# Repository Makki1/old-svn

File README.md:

# old-svn
# mainly old stuff but maybe interesting, owslave parasitic, Gira-RM 1w Interface, 1w DS2423 with attiny84..

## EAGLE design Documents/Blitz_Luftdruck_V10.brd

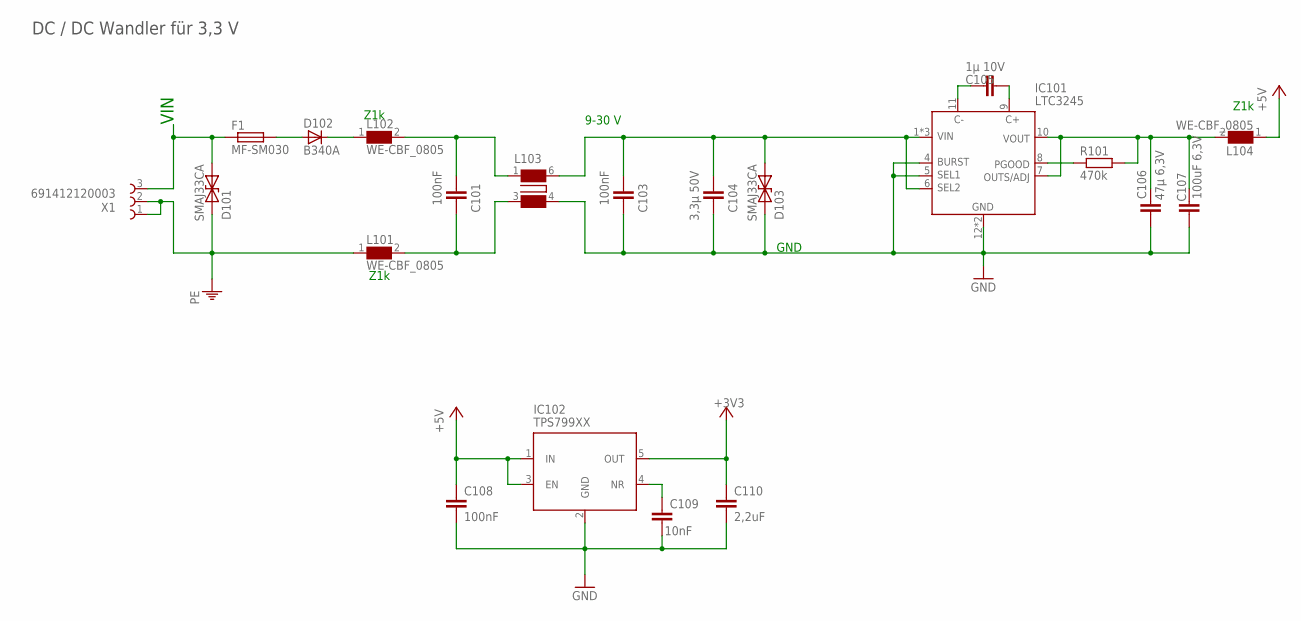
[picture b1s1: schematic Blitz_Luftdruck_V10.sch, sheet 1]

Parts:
C101, C103, C108: 100nF; C0603
C104: 3,3µ 50V; C1210TDK280
C105: 1µ 10V; C0402MUR55
C106: 47µ 6,3V; C0805TDK100
C107: 100uF 6,3V; C1206TDK180
C109: 10nF; C0402MUR55
C110: 2,2uF; C0603
D101, D103: SMAJ33CA; DIOMNP4326X262N
D102: B340A; DIOM5226X230N
F1: MF-SM030; MF-SMX
IC101: LTC3245; PSON50P400X300X80-13N
IC102: TPS799XX; SOT95P280X110-5N
L101, L102, L104: WE-CBF_0805; INDC2012X110N
L103: WE-SL3_744252...
R101: 470k; R0402
X1: 691412120003

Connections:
+3V3: C110.1, IC102.5 (OUT); also elsewhere on the board
+5V: C108.1, IC102.1 (IN), IC102.3 (EN), L104.1; also elsewhere on the board
GND: C103.1, C104.1, C106.2, C107.2, C108.2, C109.2, C110.2, D103.1 (A), IC101.4 (BURST), IC101.5 (SEL1), IC101.12 (GND), IC101.13 (GND), IC102.2 (GND), L103.4 (2); also elsewhere on the board
LTC3245C+: C105.2, IC101.9 (C+)
LTC3245C-: C105.1, IC101.11 (C-)
LTC3245VIN: C103.2, C104.2, D103.2 (C), IC101.1 (VIN), IC101.2 (VIN), IC101.3 (VIN), IC101.6 (SEL2), L103.6 (4)
LTC3245_VOUT: C106.1, C107.1, IC101.7 (ADJ), IC101.10 (VOUT), L104.2, R101.2
unnamed: D102.A, F1.2
unnamed: C101.1, L101.2, L103.3 (1)
unnamed: C101.2, L102.2, L103.1 (3)
unnamed: D102.C, L102.1
unnamed: IC101.8 (PGOOD), R101.1
unnamed: C109.1, IC102.4 (NR)
PE: D101.1 (A), L101.1, X1.1, X1.2; also elsewhere on the board
VIN: D101.2 (C), F1.1, X1.3; also elsewhere on the board

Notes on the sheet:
GND
9-30 V
Z1k
DC / DC Wandler für 3,3 V
VIN

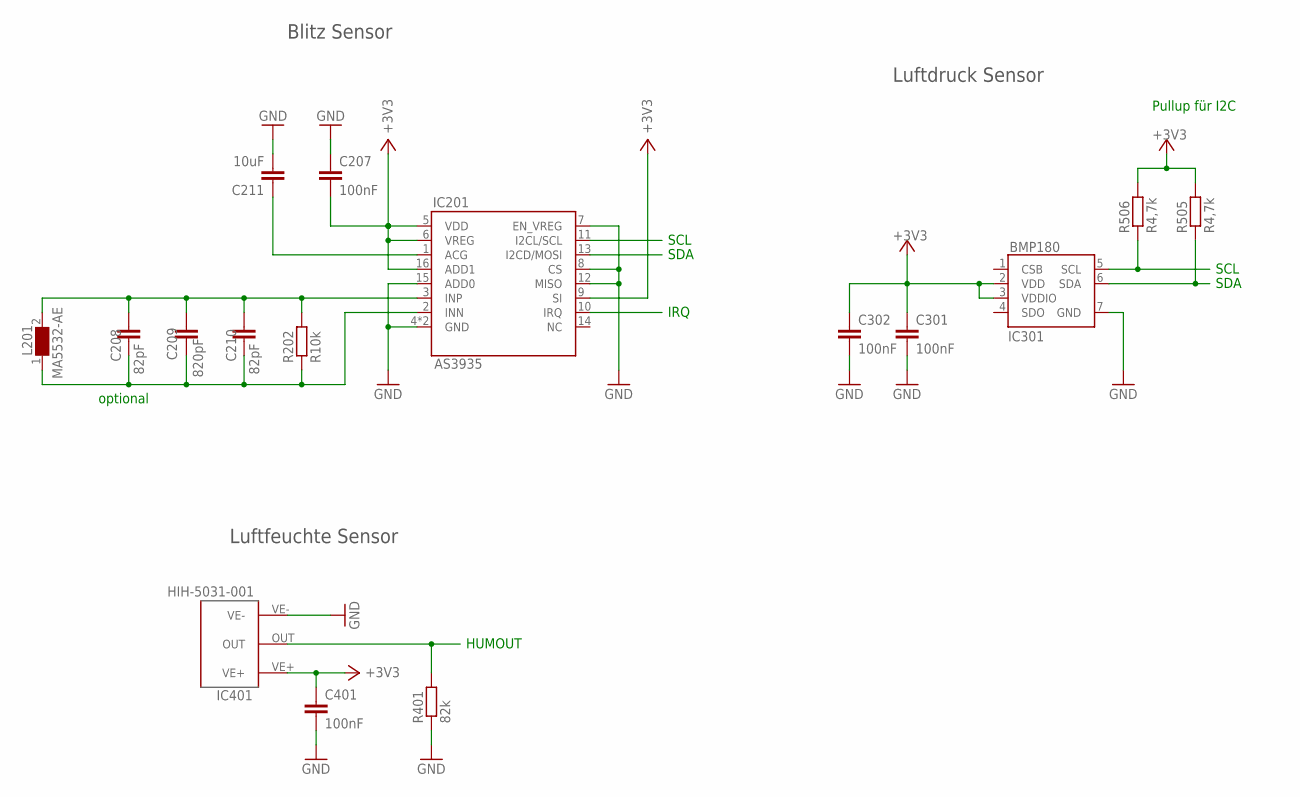
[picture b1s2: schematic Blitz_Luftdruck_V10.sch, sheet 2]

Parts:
C207, C301, C302, C401: 100nF; C0603
C208, C210: 82pF; C0603
C209: 820pF; C0603
C211: 10uF; C0805TDK100
IC201: AS3935; QFN65P400X400X80-17N
IC301: BMP180; LGA7S150X145P3X3_380X360X100N
IC401: HIH-5031-001; HIH-*03*
L201: MA5532-AE
R202: R10k; R0603VISHTHICK
R401: 82k; R0402
R505, R506: R4,7k; R0603VISHTHICK

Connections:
+3V3: C207.2, C301.1, C302.1, C401.1, IC201.5 (VDD), IC201.6 (VREG), IC201.9 (SI), IC201.16 (ADD1), IC301.2 (VDD), IC301.3 (VDDIO), IC401.VE+, R505.2, R506.2; also elsewhere on the board
GND: C207.1, C211.2, C301.2, C302.2, C401.2, IC201.4 (GND), IC201.7 (EN_VREG), IC201.8 (CS), IC201.12 (MISO), IC201.15 (ADD0), IC201.EP (GND), IC301.7 (GND), IC401.VE-, R401.1; also elsewhere on the board
HUMOUT: IC401.OUT, R401.2; also elsewhere on the board
IRQ: IC201.10 (IRQ); also elsewhere on the board
unnamed: C211.1, IC201.1 (ACG)
unnamed: C208.1, C209.1, C210.1, IC201.3 (INP), L201.2, R202.2
unnamed: C208.2, C209.2, C210.2, IC201.2 (INN), L201.1, R202.1
SCL: IC201.11 (I2CL/SCL), IC301.5 (SCL), R506.1; also elsewhere on the board
SDA: IC201.13 (I2CD/MOSI), IC301.6 (SDA), R505.1; also elsewhere on the board
SDO: IC301.4 (SDO)

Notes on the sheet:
SCL
SDA
Pullup für I2C
optional
HUMOUT
Blitz Sensor
Luftfeuchte Sensor
Luftdruck Sensor
IRQ

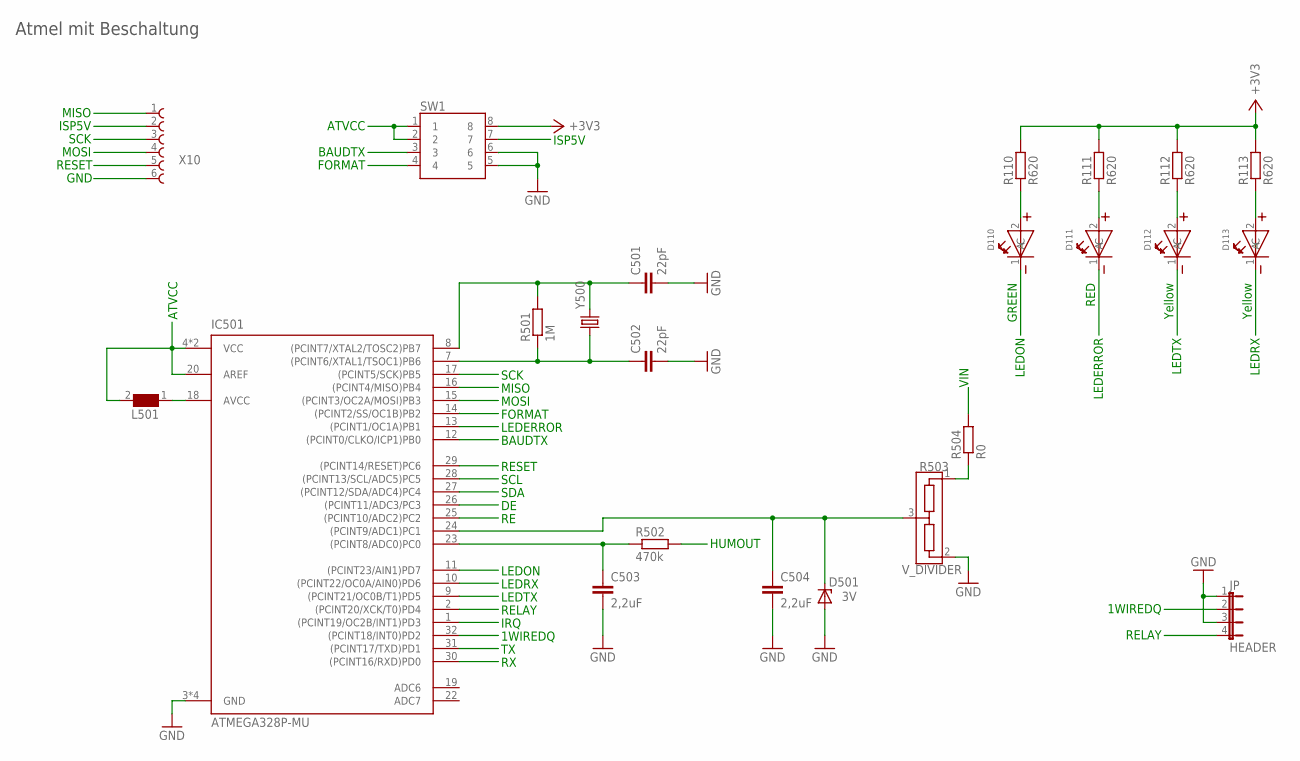
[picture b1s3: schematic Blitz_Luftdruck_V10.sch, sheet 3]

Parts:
C501, C502: 22pF; C0805TDK100
C503, C504: 2,2uF; C0603
D110: WL-SMRW156120VS75300-BRIGHTGREEN-RVS-MOUNT; WL-SMRW-1206-CYLDR-REVERSE-MOUNT
D111: WL-SMRW156120RS75300-RED-RVS-MOUNT; WL-SMRW-1206-CYLDR-REVERSE-MOUNT
D112, D113: WL-SMRW156120YS75300-YELLOW-RVS-MOUNT; WL-SMRW-1206-CYLDR-REVERSE-MOUNT
D501: 3V; SODFL3715X135N
IC501: ATMEGA328P-MU; QFN50P500X500X100-33N
JP: HEADER; SHDRV4W50P254_4X1_1016X254H850P
L501: WE-CBF_0402; 0402
R110, R111, R112, R113: R620; R0402
R501: 1M; R0402
R502: 470k; R0402
R503: V_DIVIDER; SOT95P229X117-3N
R504: R0; R0603VISHTHICK
SW1: 416131160804
X10: TC2030-IDC-NL
Y500: FOXSDLF/115-20; XTAL1170X500X450N

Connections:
1WIREDQ: IC501.32 ((PCINT18/INT0)PD2), JP.2
+3V3: R110.2, R111.2, R112.2, R113.2, SW1.8; also elsewhere on the board
ADIN24: C504.1, D501.C, IC501.24 ((PCINT9/ADC1)PC1), R503.3
ATVCC: IC501.4 (VCC), IC501.6 (VCC), IC501.20 (AREF), L501.2, SW1.1, SW1.2
BAUDTX: IC501.12 ((PCINT0/CLKO/ICP1)PB0), SW1.3
DE: IC501.26 ((PCINT11/ADC3/PC3); also elsewhere on the board
FORMAT: IC501.14 ((PCINT2/SS/OC1B)PB2), SW1.4
GND: C501.2, C502.2, C503.2, C504.2, D501.A, IC501.3 (GND), IC501.5 (GND), IC501.21 (GND), IC501.EP (GND), JP.1, JP.3, R503.2, SW1.5, SW1.6, X10.6; also elsewhere on the board
HUMIN: C503.1, IC501.23 ((PCINT8/ADC0)PC0), R502.1
HUMOUT: R502.2; also elsewhere on the board
IRQ: IC501.1 ((PCINT19/OC2B/INT1)PD3); also elsewhere on the board
ISP5V: SW1.7, X10.2
LEDERROR: D111.1 (C), IC501.13 ((PCINT1/OC1A)PB1)
LEDON: D110.1 (C), IC501.11 ((PCINT23/AIN1)PD7)
LEDRX: D113.1 (C), IC501.10 ((PCINT22/OC0A/AIN0)PD6)
LEDTX: D112.1 (C), IC501.9 ((PCINT21/OC0B/T1)PD5)
MISO: IC501.16 ((PCINT4/MISO)PB4), X10.1
MOSI: IC501.15 ((PCINT3/OC2A/MOSI)PB3), X10.4
unnamed: C502.1, IC501.7 ((PCINT6/XTAL1/TSOC1)PB6), R501.1, Y500.1
unnamed: C501.1, IC501.8 ((PCINT7/XTAL2/TOSC2)PB7), R501.2, Y500.2
unnamed: IC501.18 (AVCC), L501.1
unnamed: D110.2 (A), R110.1
unnamed: D111.2 (A), R111.1
unnamed: D112.2 (A), R112.1
unnamed: D113.2 (A), R113.1
unnamed: R503.1, R504.1
RE: IC501.25 ((PCINT10/ADC2)PC2); also elsewhere on the board
RELAY: IC501.2 ((PCINT20/XCK/T0)PD4), JP.4
RESET: IC501.29 ((PCINT14/RESET)PC6), X10.5
RX: IC501.30 ((PCINT16/RXD)PD0); also elsewhere on the board
SCK: IC501.17 ((PCINT5/SCK)PB5), X10.3
SCL: IC501.28 ((PCINT13/SCL/ADC5)PC5); also elsewhere on the board
SDA: IC501.27 ((PCINT12/SDA/ADC4)PC4); also elsewhere on the board
TX: IC501.31 ((PCINT17/TXD)PD1); also elsewhere on the board
VIN: R504.2; also elsewhere on the board

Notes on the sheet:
ISP5V
MOSI
MISO
GND
RESET
SCK
RED
GREEN
Yellow
LEDERROR
SCL
SDA
LEDON
LEDRX
LEDTX
IRQ
1WIREDQ
ATVCC
BAUDTX
FORMAT
HUMOUT
RELAY
VIN
Atmel mit Beschaltung

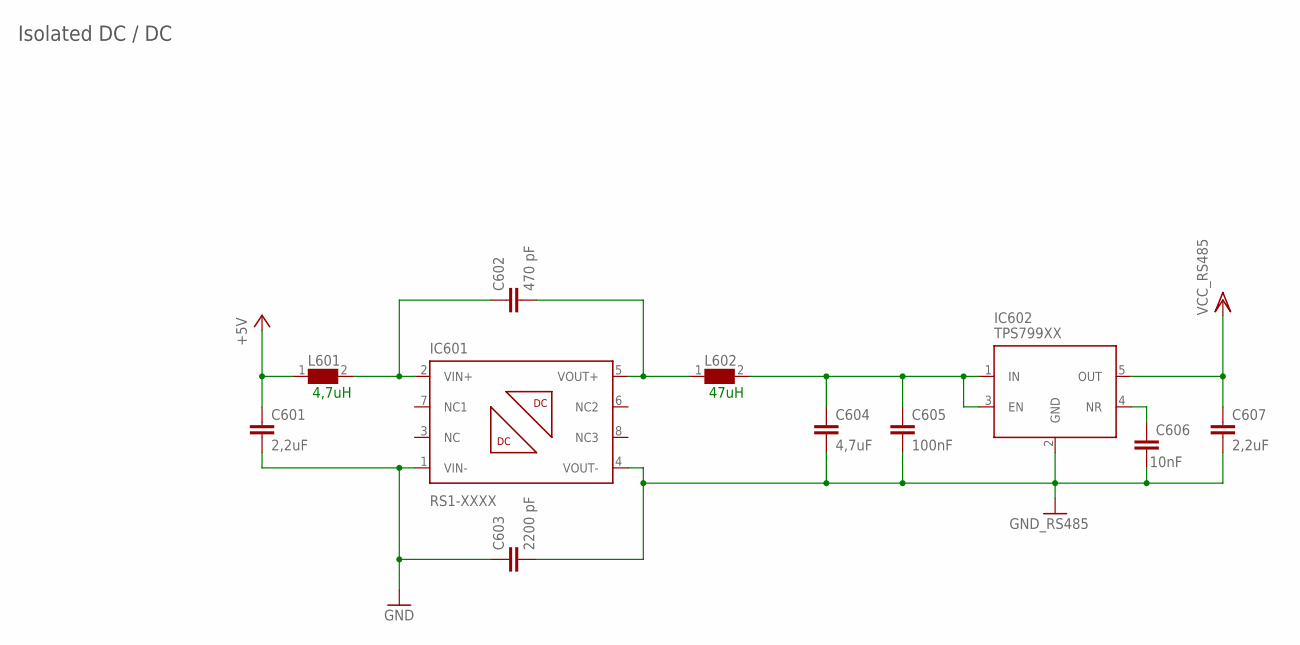
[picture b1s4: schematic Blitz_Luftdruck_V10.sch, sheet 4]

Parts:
C601: 2,2uF; C0805TDK100
C602: 470 pF; CAPC4532X155N
C603: 2200 pF; CAPC4532X155N
C604: 4,7uF; C0805TDK100
C605: 100nF; C0603
C606: 10nF; C0402MUR55
C607: 2,2uF; C0603
IC601: RS1-XXXX; R1S8-XXXX
IC602: TPS799XX; SOT95P280X110-5N
L601, L602: 0806L0806_200X160X160; INDC2016X180N

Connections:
+5V: C601.1, L601.1; also elsewhere on the board
GND: C601.2, C603.1, IC601.1 (VIN-); also elsewhere on the board
unnamed: C606.1, IC602.4 (NR)
unnamed: C604.1, C605.1, IC602.1 (IN), IC602.3 (EN), L602.2
unnamed: C602.2, IC601.5 (VOUT+), L602.1
unnamed: C602.1, IC601.2 (VIN+), L601.2
RS485_GND: C603.2, C604.2, C605.2, C606.2, C607.2, IC601.4 (VOUT-), IC602.2 (GND); also elsewhere on the board
VDD: C607.1, IC602.5 (OUT); also elsewhere on the board

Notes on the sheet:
4,7uH
47uH
Isolated DC / DC

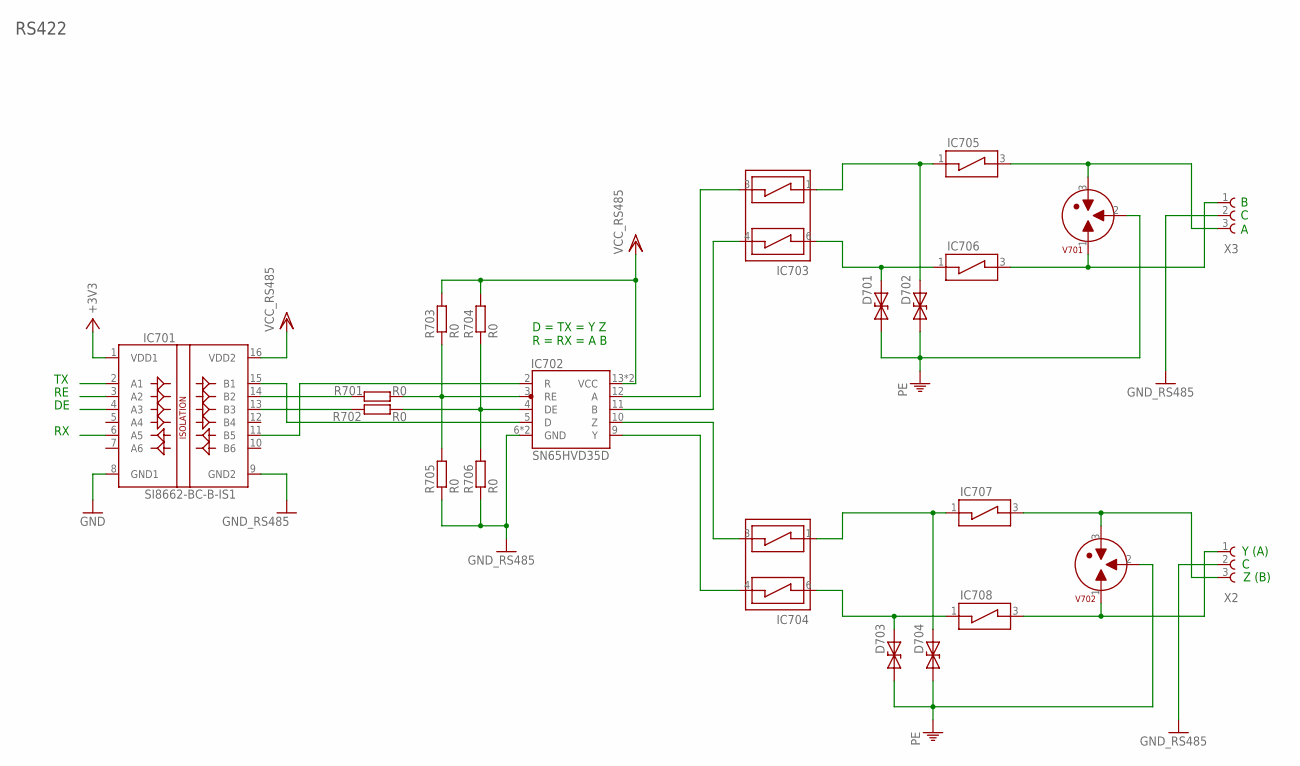
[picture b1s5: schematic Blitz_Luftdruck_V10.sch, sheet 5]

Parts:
D701, D702, D703, D704: SMA6J24CA-TP; DIOMNP5027X244N
IC701: SI8662-BC-B-IS1; SOIC127P600X175-16N
IC702: SN65HVD35D; SOIC127P600X175-14N
IC703, IC704: P40-G240-WH
IC705, IC706, IC707, IC708: TBU-CA065-200-WH; TBU-CA
R701, R702, R703, R704, R705, R706: R0; R0603VISHTHICK
V701, V702: 2030-23T-SM-RPLF; 2030-XXT-SM
X2, X3: 691412120003

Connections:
+3V3: IC701.1 (VDD1); also elsewhere on the board
DE: IC701.4 (A3); also elsewhere on the board
GND: IC701.8 (GND1); also elsewhere on the board
unnamed: IC706.3 (VIN1), V701.1, X3.1
unnamed: IC708.3 (VIN1), V702.1, X2.1
unnamed: IC702.12 (A), IC703.3 (OUT1)
unnamed: IC707.3 (VIN1), V702.3, X2.3
unnamed: D704.1 (A), IC704.1 (IN1), IC707.1 (VIN)
unnamed: D703.1 (A), IC704.6 (IN2), IC708.1 (VIN)
unnamed: IC702.4 (DE), R702.1, R704.1, R706.2
unnamed: IC705.3 (VIN1), V701.3, X3.3
unnamed: D702.1 (A), IC703.1 (IN1), IC705.1 (VIN)
unnamed: D701.1 (A), IC703.6 (IN2), IC706.1 (VIN)
unnamed: IC701.15 (B1), IC702.5 (D)
unnamed: IC702.9 (Y), IC704.4 (OUT2)
unnamed: IC701.11 (B5), IC702.2 (R)
unnamed: IC702.11 (B), IC703.4 (OUT2)
unnamed: IC702.10 (Z), IC704.3 (OUT1)
unnamed: IC702.3 (RE), R701.1, R703.1, R705.2
unnamed: IC701.13 (B3), R702.2
unnamed: IC701.14 (B2), R701.2
PE: D701.2 (C), D702.2 (C), D703.2 (C), D704.2 (C), V701.2, V702.2; also elsewhere on the board
RE: IC701.3 (A2); also elsewhere on the board
RS485_GND: IC701.9 (GND2), IC702.6 (GND), IC702.7 (GND), R705.1, R706.1, X2.2, X3.2; also elsewhere on the board
RX: IC701.6 (A5); also elsewhere on the board
TX: IC701.2 (A1); also elsewhere on the board
VDD: IC701.16 (VDD2), IC702.13 (VCC), IC702.14 (VCC), R703.2, R704.2; also elsewhere on the board

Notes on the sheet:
Z (B)
Y (A)
D = TX = Y Z R = RX = A B
RS422

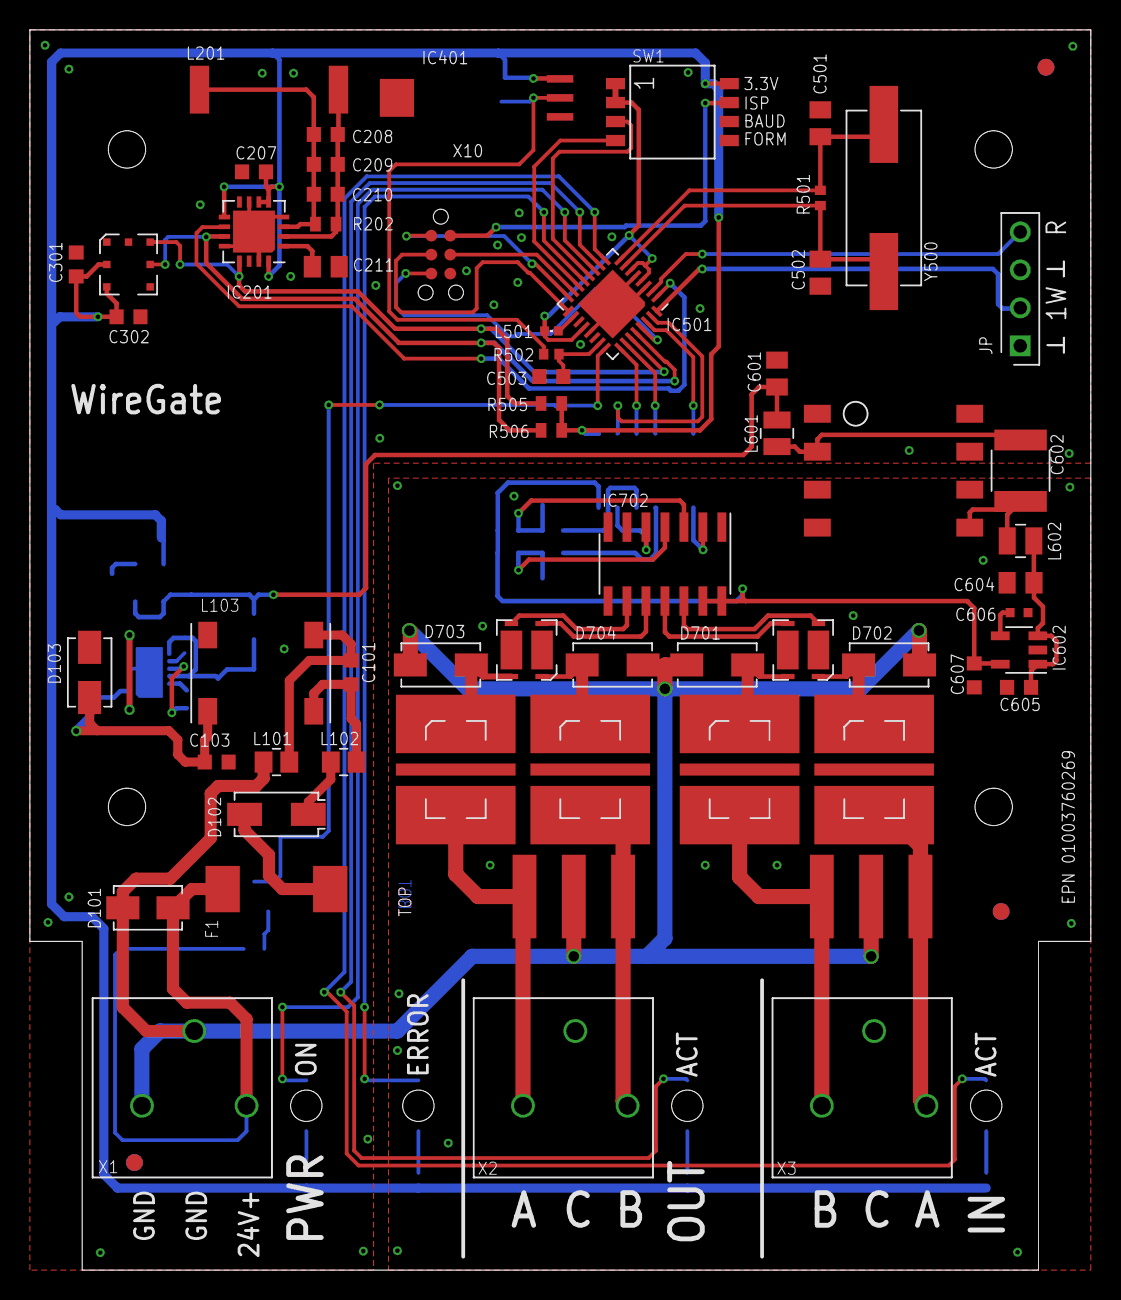
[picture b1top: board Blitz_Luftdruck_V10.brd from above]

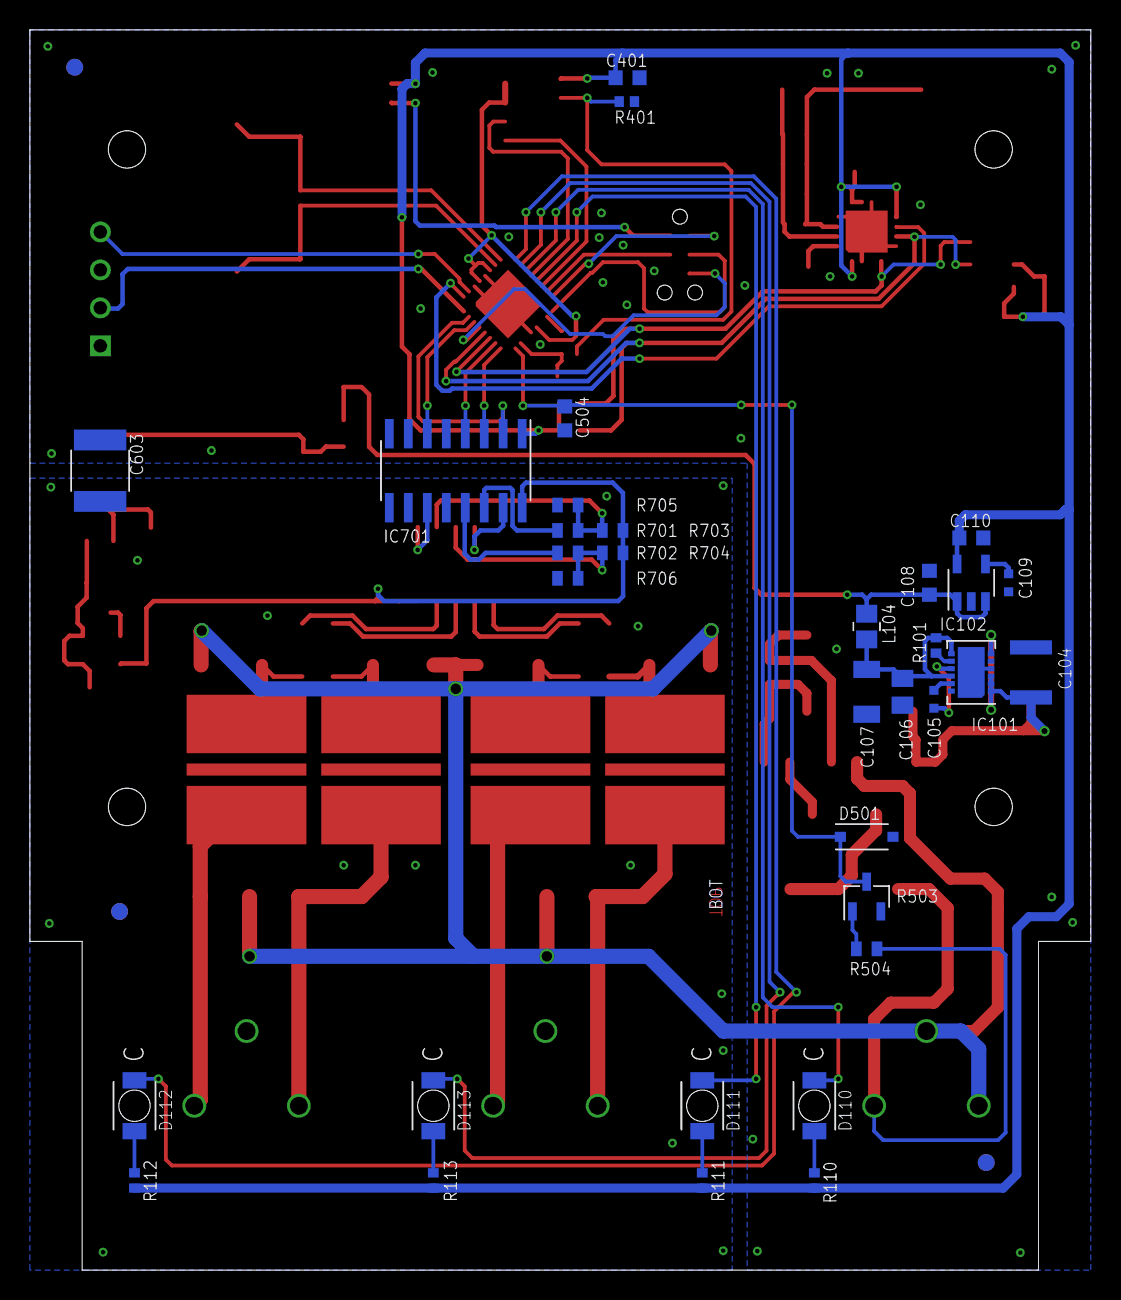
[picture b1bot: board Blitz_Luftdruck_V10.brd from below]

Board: 2 copper layers, 71.0 x 83.0 mm, 96 parts (33 on the bottom side), 74 nets.

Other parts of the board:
U$1, U$2, U$3: PASSER

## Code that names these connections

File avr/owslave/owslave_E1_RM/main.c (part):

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

#if defined(__AVR_ATmega48__) || (__AVR_ATmega88__) || (__AVR_ATmega328P__)
// OW_PORT Pin 4  - PD2(INT0)

//OW Pin
#define OW_PORT PORTD //1 Wire Port
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
/* TODO/FIXME: define ports for status-leds, etc
 * AVOID:
 * PB2-5: SPI
 * PC4-5: TWI
 * PC0-3: ADC0-3
 * PD5-6: PWM0 (?TC in use!)
 * PB1-2: PWM1
 * PB3/PD3: PWM2
 * PD2-3: INT0-1
 * PD0-1: USART
 * Good:
 * PD4
 * PB6-7 (XTAL)
 * PD7
 * PB0
 * PB1-5 (used by counter, collides PWM0,SPI)
 */
#define RMRXLED_PORT PORTD
#define RMRXLED_DDR DDRD
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
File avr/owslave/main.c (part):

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#include "debug.h"

#ifdef __AVR_ATtiny25__
// OW_PORT Pin 7  - PB2

//OW Pin
#define OW_PORT PORTB //1 Wire Port
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#endif // __AVR_ATtiny25__

#if defined(__AVR_ATtiny2313A__) || defined(__AVR_ATtiny2313__)
// OW_PORT Pin 6  - PD2

//OW Pin
#define OW_PORT PORTD //1 Wire Port
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
#define INIT_COUNTER_PINS /* Counter Interrupt */\
                        GIMSK|=(1<<PCIE);\
                        PORTB |= ( (1<<PB1) | (1<<PB2) | (1<<PB3) | (1<<PB4) ); /* activate internal Pull-Up  */ \
                        PCMSK=(1<<PCINT1)|(1<<PCINT2)|(1<<PCINT3)|(1<<PCINT4);    \
                        DDRB &=~((1<<PINB1)|(1<<PINB2)|(1<<PINB3)|(1<<PINB4)); \
                        istat=PINB; \
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

#if defined(__AVR_ATmega48__) || (__AVR_ATmega644__)
// OW_PORT Pin 4  - PD2(INT0)

//OW Pin
#define OW_PORT PORTD //1 Wire Port
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                  /* MAYBE use 16bit TC1 for this @4MHz?? */ \
                  /* FIXME: init TC1 for PWM/internal time-clock */ \
                  /* FIXED: test wether TC0 can be still used for PWM->YES 490Hz- though it "flickers" for 2x20ms when 1-Wire is active: */ \
                  DDRD |= ((1<<PIND5)|(1<<PIND6)); /* PD5& as output */ \
                  TCCR0A |= ((2<<COM0A0) | (2<<COM0B0) | (3<<WGM00)); /* enable output-compare-match */ \
                  OCR0A = 128; OCR0B = 192; /* set dummy-values 50/75% */ \
                  /* TCNT1 - Test */ \
                  DDRB |= ((1<<PINB1)|(1<<PINB2)); /* PB1&2 as output */ \
                  TIMSK1 |= (1<<TOIE1); TIFR1 |= (1<<TOV1); /* enable overflow int for timer1 */ \
                  TCCR1A |= (1<<COM1A1)|(1<<COM1B1)|(1<<WGM10); /* 8bit Fast-PWM 0<<COM1A0 0<<COM1B0 0<<WGM11 */ \
                  TCCR1B |= (1<<WGM12)|(1<<CS11)|(1<<CS10); /* 0<<WGM13 FastPWM - Clock for TIM1 /1024 ; /256 ohne |(1<<CS10) */ \
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                  /* /256 gives 125Hz? 8ms = 1222 * ++ in OVF per 10s
                   * every 32us ?

                  /* !! FIXME: must set DDRB PB0/PB1 to output and remove counter below! for PWM to work FIXME !! */
                  // :1024 = every 7812,5 uS?
                  /* Atmega48: PD5/PD6; Attiny2313: PB2/PD5 */ \
                  /* FIXME: disable ADC etc to save power here? */

#define PWRSAVE_AVR PRR = (1<<PRTWI)|(1<<PRTIM2)|(1<<PRSPI)|(1<<PRADC); /* power down TWI, TIMCNT2, leave USART |(1<<PRUSART0) on for debug! */ \
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
#define INIT_COUNTER_PINS /* Init counter pins */ \
                        PCICR=(1<<PCIE0); /* enable PCINT0..7 global */ \
/*                        PORTB |= ( (1<<PB1) | (1<<PB2) ); */ \
                        PORTB |= ( (1<<PB3) | (1<<PB4) ); /* activate internal Pull-Up PB1-4 */ \
/*                        PCMSK0|= ((1<<PCINT1)|(1<<PCINT2)); */ \
                        PCMSK0|= ((1<<PCINT3)|(1<<PCINT4)); /* enable PCINT1-4 PB1-4 */ \
/*                        DDRB &=~((1<<PINB1)|(1<<PINB2)); */ \
                        DDRB &=~((1<<PINB3)|(1<<PINB4)); /* PB1-4 as input */ \
                        istat=PINB; \

/* FIXME: !! nonsense ! just to emulate DS18B20 !! */
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
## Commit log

2017-08-15 initial commit of old svn
2017-08-24 rename
2017-08-25 lirc 0.9.0 ubuntu package - patch lirc_atiusb

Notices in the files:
avr/owslave/main.c:
This program is free software: you can redistribute it and/or modify
it under the terms of the GNU General Public License as published by
the Free Software Foundation, either version 3 of the License, or
any later version.
Copyright (C) 2012  Tobias Mueller mail (at) tobynet.de
Documents/Blitz_Luftdruck_V10.brd:
(c) 2011-08-18, Stefan Werner, Elaborated Networks GmbH
parts and their libraries:
EN_Kondensator: (c) 2011 by Stefan Werner, Elaborated Networks GmbH
EN_Kondensator: (c) 2013 by Michael Simbuerger, Elaborated Networks GmbH
